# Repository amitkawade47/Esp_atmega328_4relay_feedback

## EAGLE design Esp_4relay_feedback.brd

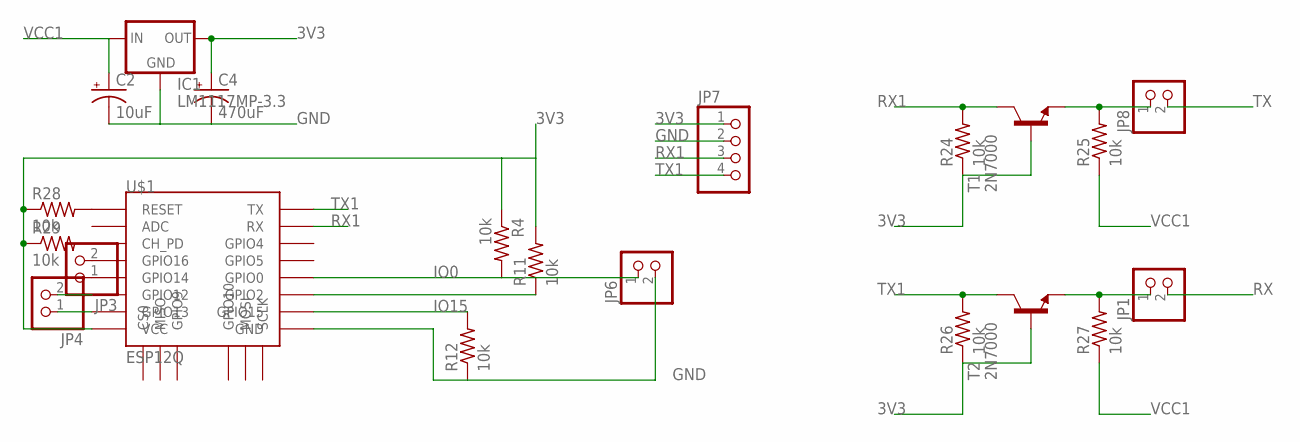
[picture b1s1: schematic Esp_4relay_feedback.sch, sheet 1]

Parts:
C2: 10uF; E2,5-6
C4: 470uF; E5-8,5
IC1: LM1117MP-3.3; SOT223
JP1, JP3, JP4, JP6, JP8: PINHD-1X2; 1X02
JP7: PINHD-1X4; 1X04
R4, R11, R12, R24, R25, R26, R27, R28, R29: 10k; 0207/10
T1, T2: 2N7000; TO92-CBE
U$1: ESP12Q

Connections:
3V3: C4.+, IC1.2 (OUT), IC1.4 (OUT), JP7.1, R4.1, R11.2, R24.1, R26.1, R28.1, R29.1, T1.B, T2.B, U$1.VCC
GND: C2.-, C4.-, IC1.1 (GND), JP6.2, JP7.2, R12.1, U$1.GND; also elsewhere on the board
IO0: JP6.1, R4.2, U$1.GPIO0
IO15: R12.2, U$1.GPIO15
unnamed: R11.1, U$1.GPIO2
unnamed: JP1.1, R27.2, T2.E
unnamed: JP8.1, R25.2, T1.E
unnamed: R29.2, U$1.CH_PD
unnamed: R28.2, U$1.RESET
unnamed: JP3.1, U$1.GPIO14
unnamed: JP3.2, U$1.GPIO16
unnamed: JP4.1, U$1.GPIO13
unnamed: JP4.2, U$1.GPIO12
RX: JP1.2; also elsewhere on the board
RX1: JP7.3, R24.2, T1.C, U$1.RX
TX: JP8.2; also elsewhere on the board
TX1: JP7.4, R26.2, T2.C, U$1.TX
VCC1: C2.+, IC1.3 (IN), R25.1, R27.1; also elsewhere on the board

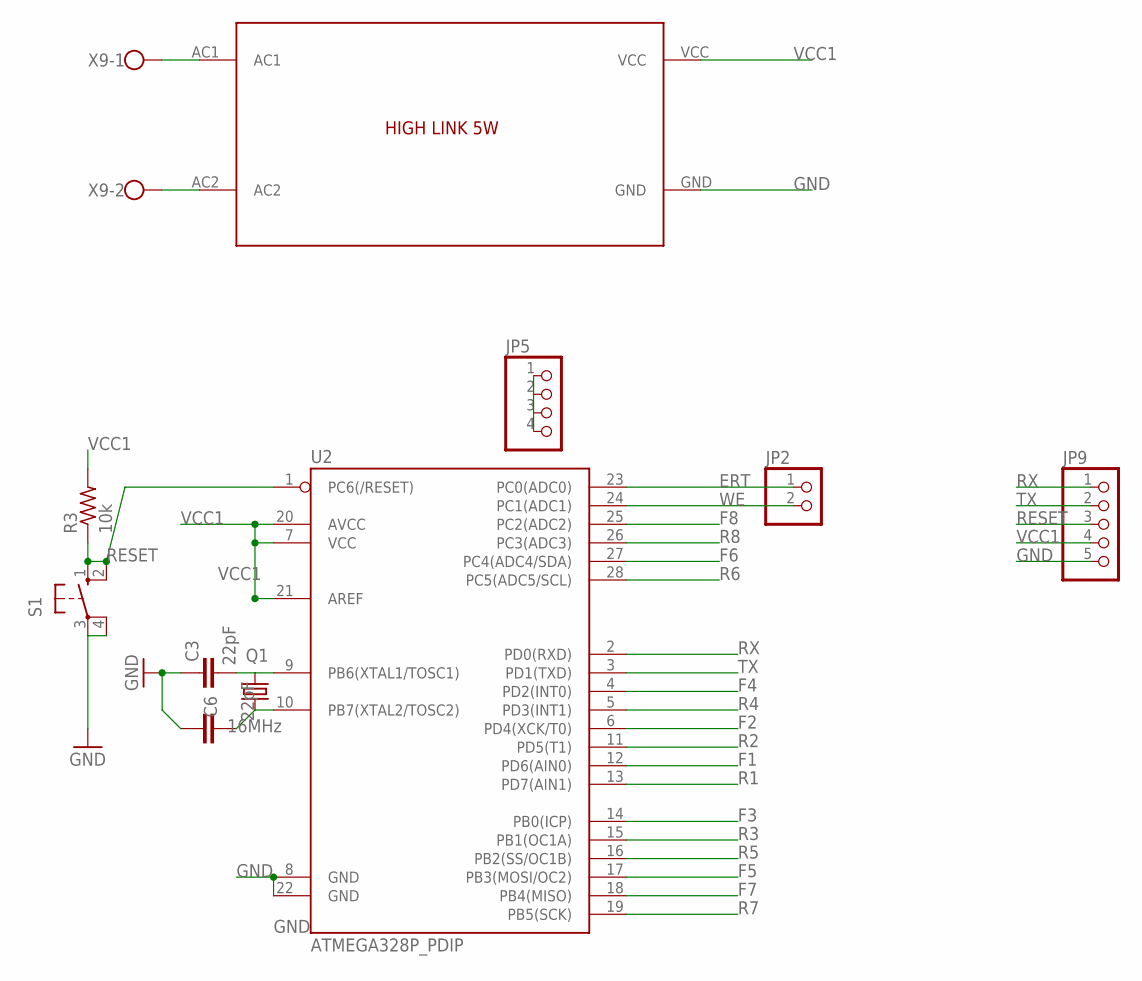
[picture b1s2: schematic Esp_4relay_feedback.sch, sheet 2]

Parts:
C3, C6: 22pF; CAP-PTH-SMALL
JP2: PINHD-1X2; 1X02
JP5: PINHD-1X4; 1X04
JP9: PINHD-1X5; 1X05
Q1: 16MHz; HC49US
R3: 10k; 0207/10
S1: 10-XX; B3F-10XX
U2: ATMEGA328P_PDIP; DIL28-3
U$2: AMIT_HIGH_LINK
X9: W237-102

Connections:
ERT: JP2.1, U2.23 (PC0(ADC0))
F1: U2.12 (PD6(AIN0)); also elsewhere on the board
F2: U2.6 (PD4(XCK/T0)); also elsewhere on the board
F3: U2.14 (PB0(ICP)); also elsewhere on the board
F4: U2.4 (PD2(INT0)); also elsewhere on the board
F5: U2.17 (PB3(MOSI/OC2)); also elsewhere on the board
F6: U2.27 (PC4(ADC4/SDA)); also elsewhere on the board
F7: U2.18 (PB4(MISO)); also elsewhere on the board
F8: U2.25 (PC2(ADC2)); also elsewhere on the board
GND: C3.1, C6.1, JP5.1, JP5.2, JP5.3, JP5.4, JP9.5, S1.3, S1.4 (P1), U2.8 (GND), U2.22 (GND), U$2.GND; also elsewhere on the board
unnamed: C3.2, Q1.2, U2.9 (PB6(XTAL1/TOSC1))
unnamed: C6.2, Q1.1, U2.10 (PB7(XTAL2/TOSC2))
unnamed: U$2.AC1, X9.1
unnamed: U$2.AC2, X9.2
R1: U2.13 (PD7(AIN1)); also elsewhere on the board
R2: U2.11 (PD5(T1)); also elsewhere on the board
R3: U2.15 (PB1(OC1A)); also elsewhere on the board
R4: U2.5 (PD3(INT1)); also elsewhere on the board
R5: U2.16 (PB2(SS/OC1B)); also elsewhere on the board
R6: U2.28 (PC5(ADC5/SCL)); also elsewhere on the board
R7: U2.19 (PB5(SCK)); also elsewhere on the board
R8: U2.26 (PC3(ADC3)); also elsewhere on the board
RESET: JP9.3, R3.1, S1.1 (S), S1.2 (S1), U2.1 (PC6(/RESET))
RX: JP9.1, U2.2 (PD0(RXD)); also elsewhere on the board
TX: JP9.2, U2.3 (PD1(TXD)); also elsewhere on the board
VCC1: JP9.4, R3.2, U2.7 (VCC), U2.20 (AVCC), U2.21 (AREF), U$2.VCC; also elsewhere on the board
WE: JP2.2, U2.24 (PC1(ADC1))

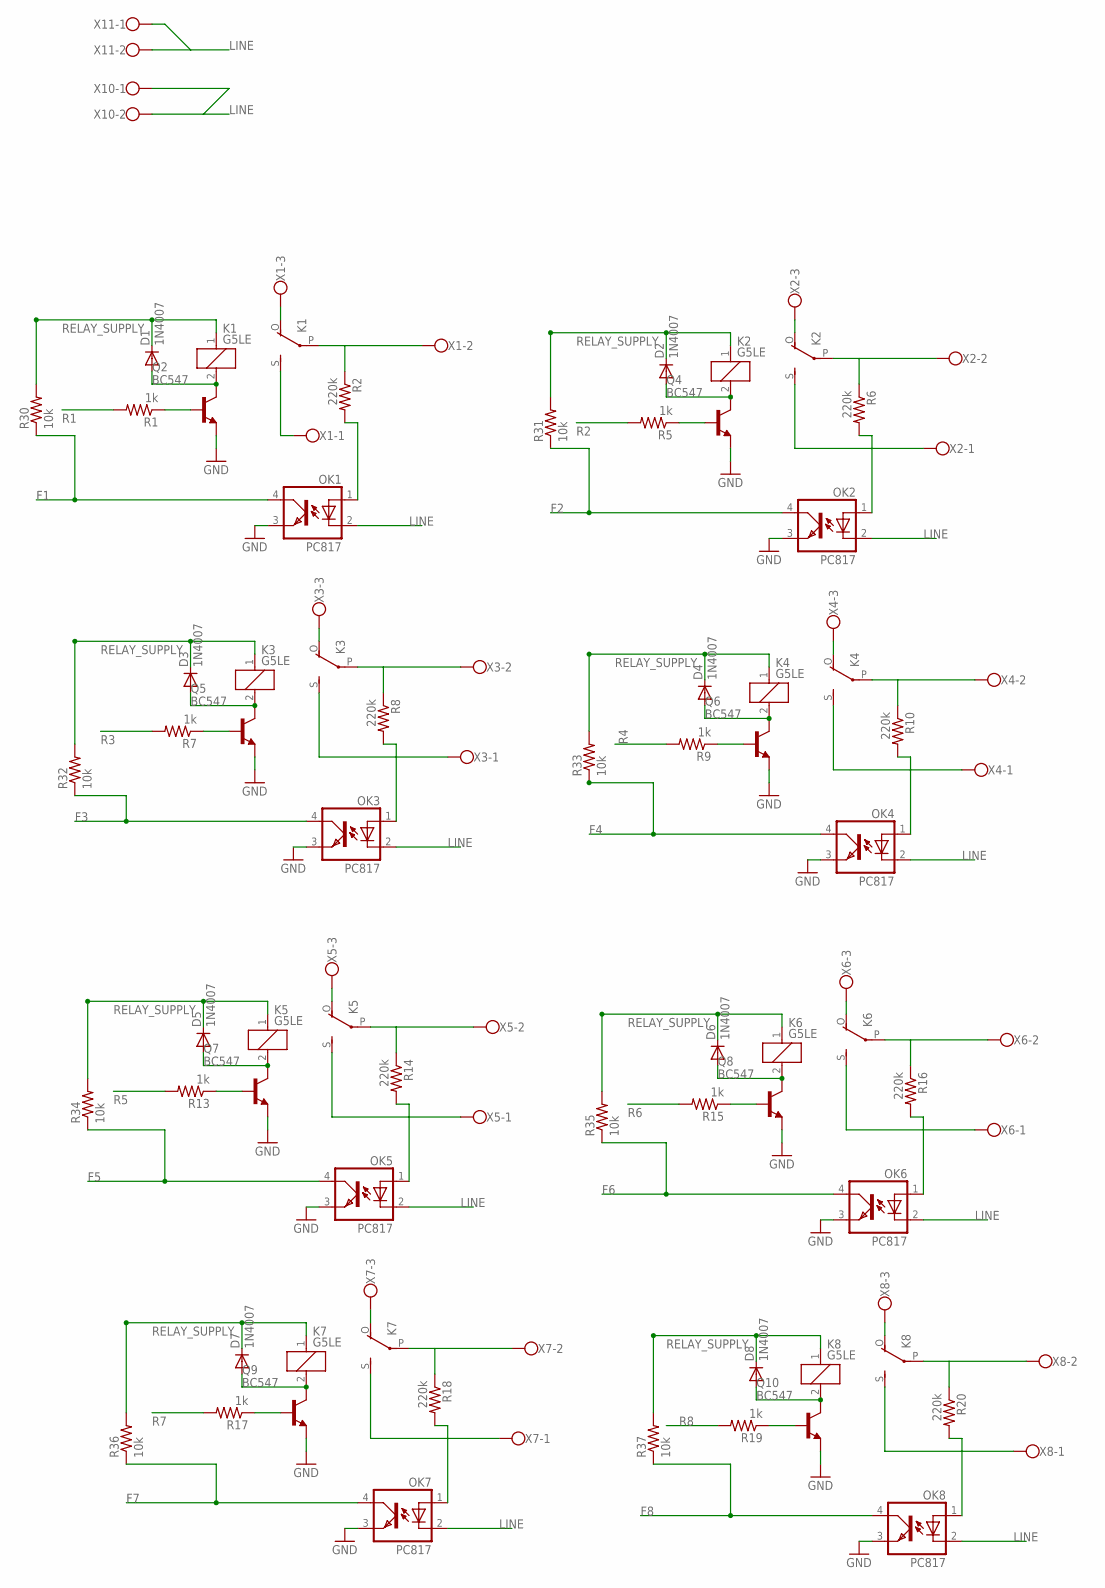
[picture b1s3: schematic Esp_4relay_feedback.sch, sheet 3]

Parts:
D1, D2, D3, D4, D5, D6, D7, D8: 1N4007; DO41-10
K1, K2, K3, K4, K5, K6, K7, K8: G5LE
OK1, OK2, OK3, OK4, OK5, OK6, OK7, OK8: PC817; DIL04
Q2, Q4, Q5, Q6, Q7, Q8, Q9, Q10: BC547; TO92-EBC
R1, R5, R7, R9, R13, R15, R17, R19: 1k; 0207/10
R2, R6, R8, R10, R14, R16, R18, R20: 220k; 0207/10
R30, R31, R32, R33, R34, R35, R36, R37: 10k; 0207/5V
X1, X2, X3, X4, X5, X6, X7, X8: W237-103; MPN 237-103
X10, X11: W237-102

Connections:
F1: OK1.4 (COL), R30.1; also elsewhere on the board
F2: OK2.4 (COL), R31.1; also elsewhere on the board
F3: OK3.4 (COL), R32.1; also elsewhere on the board
F4: OK4.4 (COL), R33.1; also elsewhere on the board
F5: OK5.4 (COL), R34.1; also elsewhere on the board
F6: OK6.4 (COL), R35.1; also elsewhere on the board
F7: OK7.4 (COL), R36.1; also elsewhere on the board
F8: OK8.4 (COL), R37.1; also elsewhere on the board
GND: OK1.3 (EMIT), OK2.3 (EMIT), OK3.3 (EMIT), OK4.3 (EMIT), OK5.3 (EMIT), OK6.3 (EMIT), OK7.3 (EMIT), OK8.3 (EMIT), Q2.E, Q4.E, Q5.E, Q6.E, Q7.E, Q8.E, Q9.E, Q10.E; also elsewhere on the board
LINE: OK1.2 (C), OK2.2 (C), OK3.2 (C), OK4.2 (C), OK5.2 (C), OK6.2 (C), OK7.2 (C), OK8.2 (C), X10.1, X10.2, X11.1, X11.2
unnamed: K1.P, R2.1, X1.2
unnamed: OK1.1 (A), R2.2
unnamed: K1.S, X1.1
unnamed: K2.P, R6.1, X2.2
unnamed: K2.S, X2.1
unnamed: Q2.B, R1.1
unnamed: D1.A, K1.2, Q2.C
unnamed: Q4.B, R5.1
unnamed: D2.A, K2.2, Q4.C
unnamed: K2.O, X2.3
unnamed: OK2.1 (A), R6.2
unnamed: K3.P, R8.1, X3.2
unnamed: K3.S, X3.1
unnamed: Q5.B, R7.1
unnamed: D3.A, K3.2, Q5.C
unnamed: K3.O, X3.3
unnamed: OK3.1 (A), R8.2
unnamed: K4.P, R10.1, X4.2
unnamed: K4.S, X4.1
unnamed: Q6.B, R9.1
unnamed: D4.A, K4.2, Q6.C
unnamed: K1.O, X1.3
unnamed: K4.O, X4.3
unnamed: OK4.1 (A), R10.2
unnamed: K5.P, R14.1, X5.2
unnamed: K5.S, X5.1
unnamed: Q7.B, R13.1
unnamed: D5.A, K5.2, Q7.C
unnamed: K5.O, X5.3
unnamed: OK5.1 (A), R14.2
unnamed: K6.P, R16.1, X6.2
unnamed: K6.S, X6.1
unnamed: Q8.B, R15.1
unnamed: D6.A, K6.2, Q8.C
unnamed: K6.O, X6.3
unnamed: OK6.1 (A), R16.2
unnamed: K7.P, R18.1, X7.2
unnamed: K7.S, X7.1
unnamed: Q9.B, R17.1
unnamed: D7.A, K7.2, Q9.C
unnamed: K7.O, X7.3
unnamed: OK7.1 (A), R18.2
unnamed: K8.P, R20.1, X8.2
unnamed: K8.S, X8.1
unnamed: Q10.B, R19.1
unnamed: D8.A, K8.2, Q10.C
unnamed: K8.O, X8.3
unnamed: OK8.1 (A), R20.2
R1: R1.2; also elsewhere on the board
R2: R5.2; also elsewhere on the board
R3: R7.2; also elsewhere on the board
R4: R9.2; also elsewhere on the board
R5: R13.2; also elsewhere on the board
R6: R15.2; also elsewhere on the board
R7: R17.2; also elsewhere on the board
R8: R19.2; also elsewhere on the board
RELAY_SUPPLY: D1.C, D2.C, D3.C, D4.C, D5.C, D6.C, D7.C, D8.C, K1.1, K2.1, K3.1, K4.1, K5.1, K6.1, K7.1, K8.1, R30.2, R31.2, R32.2, R33.2, R34.2, R35.2, R36.2, R37.2; also elsewhere on the board

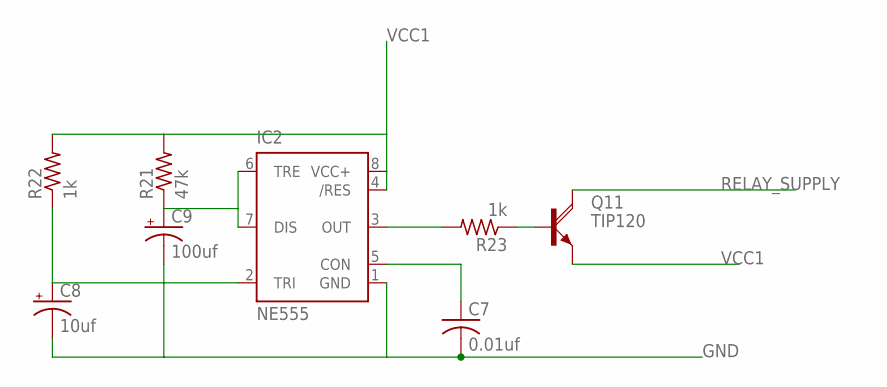
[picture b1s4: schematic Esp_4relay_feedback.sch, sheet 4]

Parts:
C7: 0.01uf; C025-025X050
C8: 10uf; E2,5-6
C9: 100uf; E2,5-6
IC2: NE555; DIL-08
Q11: TIP120; TO220AH
R21: 47k; 0207/10
R22, R23: 1k; 0207/10

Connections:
GND: C7.2, C8.-, C9.-, IC2.1 (GND); also elsewhere on the board
unnamed: C9.+, IC2.6 (TRE), IC2.7 (DIS), R21.1
unnamed: C8.+, IC2.2 (TRI), R22.1
unnamed: C7.1, IC2.5 (CON)
unnamed: IC2.3 (OUT), R23.2
unnamed: Q11.B, R23.1
RELAY_SUPPLY: Q11.C; also elsewhere on the board
VCC1: IC2.4 (/RES), IC2.8 (VCC+), Q11.E, R21.2, R22.2; also elsewhere on the board

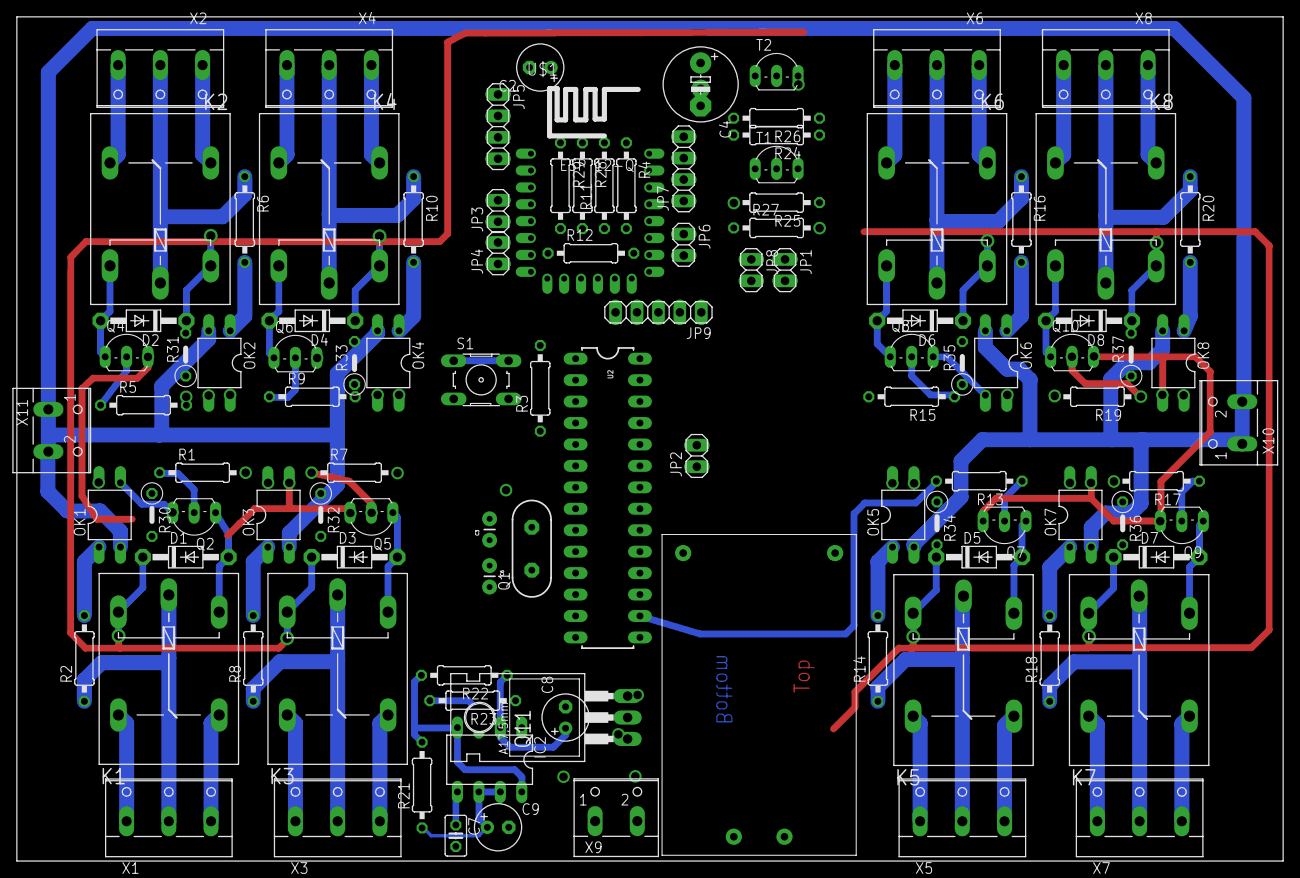
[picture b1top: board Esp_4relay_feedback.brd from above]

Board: 2 copper layers, 150.0 x 100.0 mm, 106 parts (1 on the bottom side), 96 nets.

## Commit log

2018-02-27 schematic details
    added following to schematic:
    atmega328 with esp12e
    4 relays with feedback
2018-02-28 added 8 relays
    8 relays arranged in 4 up-down manner with
    esp and atmega328 at left side.
    routing 70% completed.
2018-02-28 routing done
    board routing completed 100%
2018-03-01 component placing changed
    Controller and esp placed in between relays.
    routing done
    PCB size : 130X95mm
2018-03-01 pdf added
    added
    bottom layer pdf
    top layer pdf
    both side pdf
2018-03-01 top_layer mirror pdf
    top layer in mirror pdf added.
    both layer added in single pdf
2018-03-12 polygon added.
    polygon added.
2018-03-12 pdf,bom removed
    previous designe pdfs and bom removed
2018-03-12 feature added
    added power on delay for relay supply.
    added logic level for esp to atmega328 communication.
2018-03-12 Esp pull up added
    pull up for reset and chpd.
2018-03-12 pad removed from top side
    top side pad overlaped with vias,
    top side pdf contains only tracks n vias.
2018-03-15 PCB Layout changed
    majority component soldering is at bottom level.
    made above change for easyness of inhouse development.
2018-03-23 schematic change
    feedback circuit connection changed
    added tip127 to control relay power supply.
    made separate supply for relay and controller.
2018-03-23 PDF
    top bottom layout pdf added.
    top side is mirrored.
2018-03-26 PDF
    final pdf added.
    developed PCB with this design
2018-03-27 schematic changes
    EL814 pull up added.
    HIGH LINK 5W supply added

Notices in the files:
parts and their libraries:
SparkFun-DigitalIC: Licensing: Creative Commons ShareAlike 4.0 International - https://creativecommons.org/licenses/by-sa/4.0
